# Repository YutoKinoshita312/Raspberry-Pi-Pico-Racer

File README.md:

# Raspberry-Pi-Pico-Racer

RaspberryPiPicoを使用したロボトレーサーの回路図です。
この回路を参考に回路を作ることは可能です。必ず下記までご連絡ください。

マイコン：Raspberry Pi Pico
モータードライバー：DRV8835 ※DRV8836でも可能。今回は秋月電子で販売している「DRV8835使用ステッピング&DCモータドライバモジュール」を使用しました。
DCDCコンバーターLXDC55使用DCDCコンバーターキット (降圧 3.3V)(秋月電子)
バッテリー：3.3V以上なら何でもOKだと思う。↑があるので。必ずLXDC55使用DCDCコンバーターキット (降圧 3.3V)のデータシート(秋月電子のHPにある)を確認してください。
DCモーター：DCモーターなら何でもいい。
センサ：アナログセンサを採用。センサのLEDは赤外線LEDを推奨する。

連絡先
メール：kinoshi312@icloud.com
Twitter(現X)：wakabayashi0725

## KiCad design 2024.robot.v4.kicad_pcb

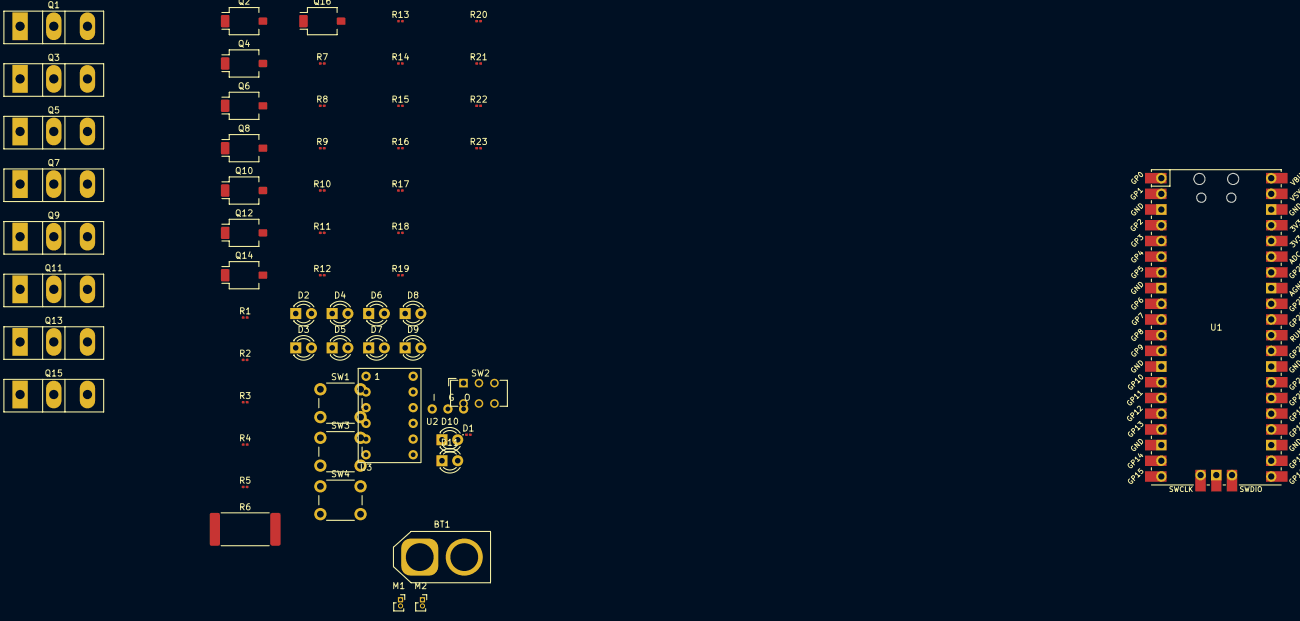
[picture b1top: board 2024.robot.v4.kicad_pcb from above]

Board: 2 copper layers, 60 parts (0 on the bottom side), 52 nets, no tracks yet.

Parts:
BT1: Battery_Cell; AMASS_XT60-F_1x02_P7.20mm_Vertical
D1: LED; LED_0201_0603Metric
D2, D3, D4, D5, D6, D7, D8, D9, D10, D11: LED; LED_D3.0mm
M1, M2: Motor_DC; PinSocket_1x02_P1.00mm_Vertical
Q1, Q3, Q5, Q7, Q9, Q11, Q13, Q15: NJFET; TO-247-3_Vertical
Q2, Q4, Q6, Q8, Q10, Q12, Q14, Q16: Q_Photo_NPN_CE; Osram_SFH2440
R1, R2, R3, R4: 47k; C_0201_0603Metric
R5, R7, R8, R9, R10, R11, R12, R13, R14, R15, R16, R17, R18, R19, R20, R21, R22, R23: 1k; C_0201_0603Metric
R6: 1k; R_4020_10251Metric_Pad1.65x5.30mm_HandSolder
SW1, SW3, SW4: SW_Omron_B3FS; SW_PUSH_6mm_H7.3mm
SW2: SW_SPST; SW_CuK_JS202011CQN_DPDT_Straight
U1: Pico; RPi_Pico_SMD_TH
U2: AE-LXDC55-3.3V
U3: DRV8835

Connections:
+3.3V: D1.2 (A), D10.2 (A), D11.2 (A), R5.1, R7.1, R8.1, R9.1, R10.1, R11.1, R12.1, R13.1, R14.1, R15.1, R16.1, R17.1, R18.1, R19.1, R20.1, R21.1, U1.36 (3V3), U3.12
BATT: U1.39 (VSYS), U3.1 (Input)
GND: BT1.2 (-), Q1.3 (S), Q2.2 (E), Q3.3 (S), Q4.2 (E), Q5.3 (S), Q6.2 (E), Q7.3 (S), Q8.2 (E), Q9.3 (S), Q10.2 (E), Q11.3 (S), Q12.2 (E), Q13.3 (S), Q14.2 (E), Q15.3 (S), Q16.2 (E), R1.2, R2.2, R3.2, R4.2, SW1.1, SW3.1, SW4.1, U1.3 (GND), U1.8 (GND), U1.18 (GND), U1.23 (GND), U1.28 (GND), U1.38 (GND), U1.42 (GND), U3.6
LED-01: Q2.1 (C), R7.2, U1.9 (GPIO6)
LED-02: Q4.1 (C), R9.2, U1.10 (GPIO7)
LED-03: Q6.1 (C), R11.2, U1.11 (GPIO8)
LED-04: Q8.1 (C), R13.2, U1.12 (GPIO9)
LED-05: Q10.1 (C), R21.2, U1.13 (GND)
LED-06: Q12.1 (C), R19.2, U1.14 (GPIO10)
LED-07: Q14.1 (C), R17.2, U1.15 (GPIO11)
LED-08: Q16.1 (C), R15.2, U1.16 (GPIO12)
Mo-01: M1.1 (+), U1.27 (GPIO21), U3.10
Mo-02: M1.2 (-), U3.9
Mo-03: M2.1 (+), U1.25 (GPIO19), U3.8
Mo-04: M2.2 (-), U1.24 (GPIO18), U3.7
Mo-MODE: U1.31 (GPIO26_ADC0), U3.11
MoOut-02: R2.1, U3.3 (Output)
MoOut-03: R3.1, U3.4
MoOut-04: R4.1, U3.5
unnamed: BT1.1 (+), SW2.1 (A)
unnamed: D1.1 (K), R6.1
unnamed: D2.2 (A), R5.2
unnamed: D2.1 (K), Q1.1 (D)
unnamed: D3.2 (A), R8.2
unnamed: D3.1 (K), Q3.1 (D)
unnamed: D4.2 (A), R10.2
unnamed: D4.1 (K), Q5.1 (D)
unnamed: D5.2 (A), R12.2
unnamed: D5.1 (K), Q7.1 (D)
unnamed: D6.2 (A), R14.2
unnamed: D6.1 (K), Q9.1 (D)
unnamed: D7.2 (A), R16.2
unnamed: D7.1 (K), Q11.1 (D)
unnamed: D8.2 (A), R18.2
unnamed: D8.1 (K), Q13.1 (D)
unnamed: D9.2 (A), R20.2
unnamed: D9.1 (K), Q15.1 (D)
unnamed: D10.1 (K), R22.1
unnamed: D11.1 (K), R23.1
unnamed: SW1.2, U1.4 (GPIO2)
unnamed: SW3.2, U1.5 (GPIO3)
unnamed: SW4.2, U1.6 (GPIO4)
unnamed: R23.2, U1.7 (GPIO5)
unnamed: R22.2, U1.29 (GPIO22)
Senser-01: Q1.2 (G), U1.17 (GPIO13)
Senser-02: Q3.2 (G), U1.19 (GPIO14)
Senser-03: Q5.2 (G), U1.20 (GPIO15)
Senser-04: Q7.2 (G), U1.1 (GPIO0), U1.2 (GPIO1)
Senser-05: Q9.2 (G), U1.34 (GPIO28_ADC2)
Senser-06: Q11.2 (G), U1.32 (GPIO27_ADC1)
Senser-07: Q13.2 (G), U1.22 (GPIO17)
Senser-08: Q15.2 (G), U1.21 (GPIO16)
